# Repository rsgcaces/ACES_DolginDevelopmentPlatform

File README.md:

# RSGC ACES: Dolgin Development Platform (DDP)
 EAGLE and Fusion 360 Design files relating to the RSGC ACES Dolgin Development Platform

## USB to TTL Serial Support
Below is an image of the DDP software serial streaming the 2D readings of the thumb joystick to a Processing sketch that dynamically presents the circular trig functions.   

## Morland Bargraph
The ATtiny84's pins were broken out with specific ACES' devices in mind. The image below shows the Morland Bargraph inserted strategically into the DDP.

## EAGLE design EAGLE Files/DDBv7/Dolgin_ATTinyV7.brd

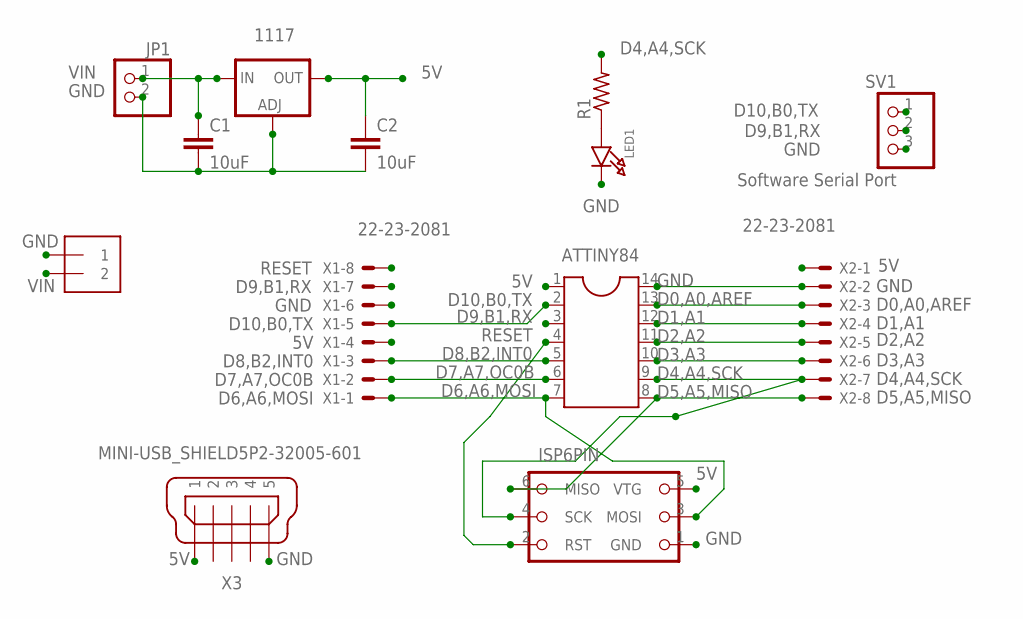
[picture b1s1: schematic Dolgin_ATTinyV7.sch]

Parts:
1117: LM1117SOT223-REFLOW; SOT223-R
ATTINY84: DIL14
C1, C2: 10uF; 1206
H1: ISP_HEADER; ICSP
J1: 1X2-3.5MM
JP1: PINHD-1X2; 1X02
LED1: LED1206; CHIPLED_1206
R1: R-US_R1206; R1206
SV1: Software Serial Port; 1X03/90
X1, X2: 22-23-2081
X3: MINI-USB_SHIELD5P2-32005-601; 32005-601

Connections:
5V: 1117.2 (OUT), ATTINY84.1, C2.1, H1.5 (VTG), X1.4, X2.1, X3.1
D0,A0,AREF: ATTINY84.13, X2.3
D1,A1: ATTINY84.12, X2.4
D2,A2: ATTINY84.11, X2.5
D3,A3: ATTINY84.10, X2.6
D4,A4,SCK: ATTINY84.9, H1.4 (SCK), R1.2, X2.7
D5,A5,MISO: ATTINY84.8, H1.6 (MISO), X2.8
D6,A6,MOSI: ATTINY84.7, H1.3 (MOSI), X1.1
D7,A7,OC0B: ATTINY84.6, X1.2
D8,B2,INT0: ATTINY84.5, X1.3
D9,B1,RX: ATTINY84.3, SV1.2, X1.7
D10,B0,TX: ATTINY84.2, SV1.3, X1.5
GND: 1117.1 (ADJ), ATTINY84.14, C1.2, C2.2, H1.1 (GND), J1.1, JP1.2, LED1.C, SV1.1, X1.6, X2.2, X3.5
unnamed: LED1.A, R1.1
RESET: ATTINY84.4, H1.2 (RST), X1.8
VIN: 1117.3 (IN), C1.1, J1.2, JP1.1

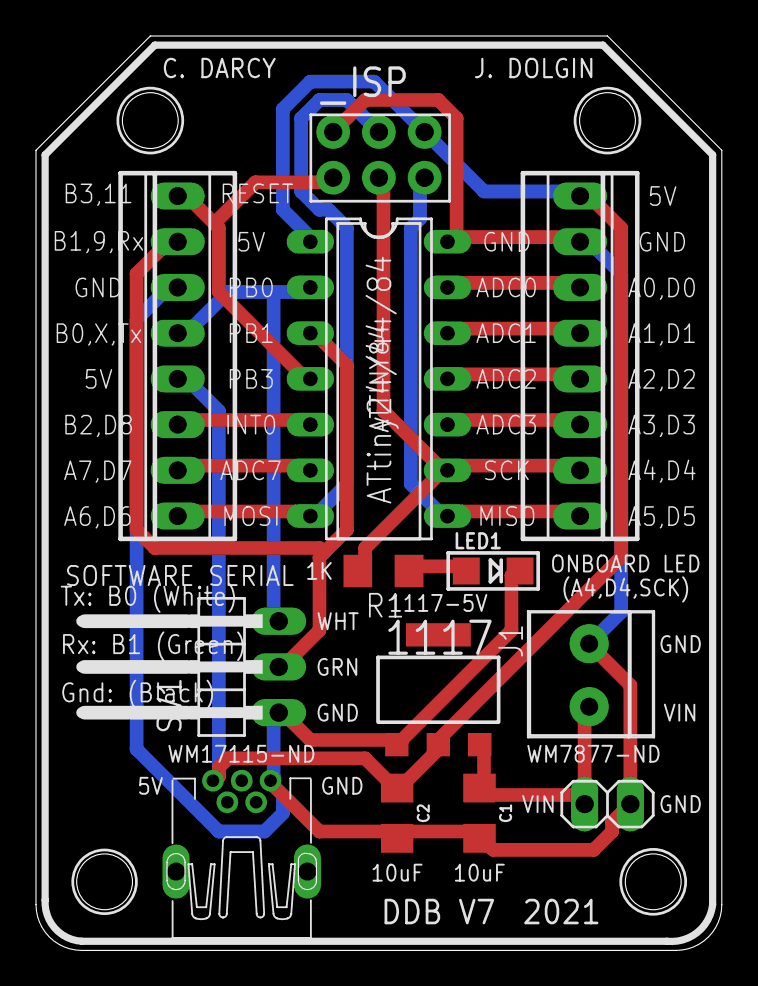
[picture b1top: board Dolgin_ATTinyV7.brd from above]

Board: 2 copper layers, 38.1 x 50.8 mm, 17 parts (1 on the bottom side), 16 nets.

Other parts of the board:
U$1, U$2, U$4: ACES_LOGO_SMALL
U$3: MEDIUM_BSILK_TEXT

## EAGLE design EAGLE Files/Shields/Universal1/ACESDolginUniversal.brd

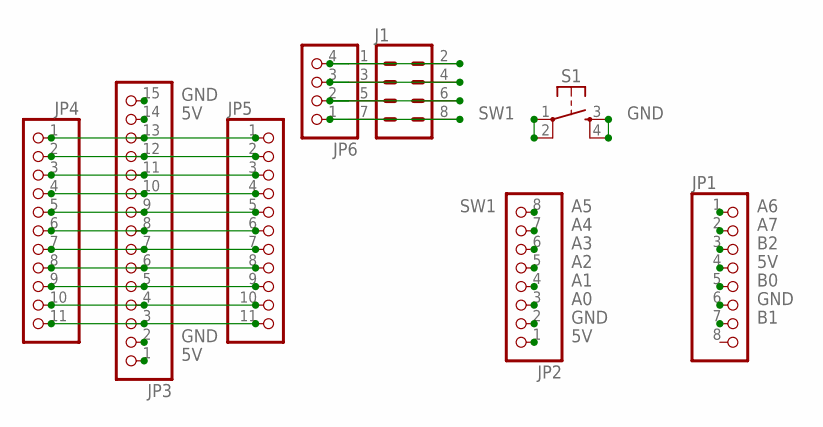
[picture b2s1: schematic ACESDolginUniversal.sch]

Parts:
J1: CONN_04X2; 2X4
JP1, JP2: PINHD-1X8; 1X08
JP3: PINHD-1X15; 1X15
JP4, JP5: PINHD-1X11; 1X11
JP6: PINHD-1X4; 1X04
S1: MOMENTARY_BUTTONS6MMSMALL; TACTILE_SWITCH_PTH_6.0MM

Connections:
5V: JP1.4, JP2.1, JP3.1, JP3.14
A0: JP2.3
A1: JP2.4
A2: JP2.5
A3: JP2.6
A4: JP2.7
A5: JP2.8
A6: JP1.1
A7: JP1.2
B0: JP1.5
B1: JP1.7
B2: JP1.3
GND: JP1.6, JP2.2, JP3.2, JP3.15, S1.3 (S), S1.4 (S1)
unnamed: J1.1, J1.2, JP6.4
unnamed: J1.3, J1.4, JP6.3
unnamed: J1.5, J1.6, JP6.2
unnamed: JP3.13, JP4.1, JP5.1
unnamed: JP3.12, JP4.2, JP5.2
unnamed: JP3.11, JP4.3, JP5.3
unnamed: JP3.10, JP4.4, JP5.4
unnamed: JP3.9, JP4.5, JP5.5
unnamed: JP3.8, JP4.6, JP5.6
unnamed: JP3.7, JP4.7, JP5.7
unnamed: JP3.6, JP4.8, JP5.8
unnamed: JP3.5, JP4.9, JP5.9
unnamed: JP3.4, JP4.10, JP5.10
unnamed: JP3.3, JP4.11, JP5.11
SW1: J1.7, J1.8, JP6.1, S1.1, S1.2 (P1)

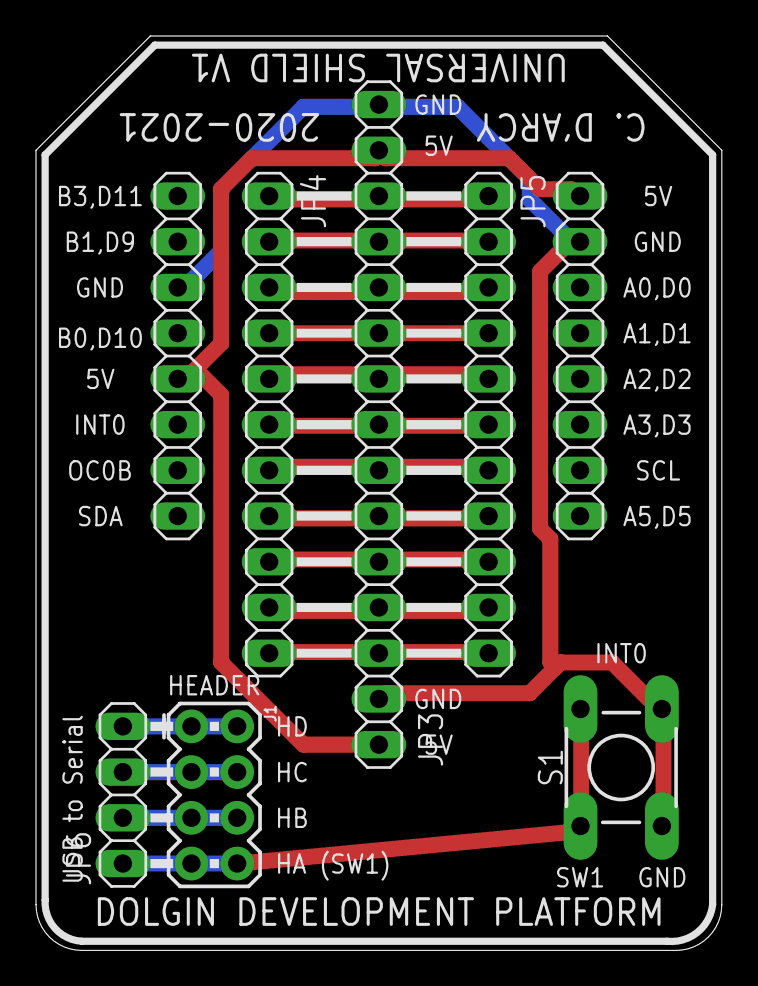
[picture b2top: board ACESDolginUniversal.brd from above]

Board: 2 copper layers, 38.1 x 50.8 mm, 12 parts (0 on the bottom side), 17 nets.

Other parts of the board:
U$1: CAUTION_ELECTRIC
U$2, U$3: SMALL_TSILK_TEXT
U$5: MEDIUM_BSILK_TEXT

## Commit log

2020-01-11 2020 01 11
2020-01-13 Added: 2020 01 13
2020-03-07 Added: 2020 03 07
    Serial support for DDP to the Arduino Serial Monitor and Plotter. Uses the Software Serial library for use with Adafruit's USB-to-Serial Cable (#954).
2020-03-07 Updated: 2020 03 07
2020-03-09 Updated: 2020 03 09
    Example of SoftwareSerial library I/O with the DDP through the use of Adafruit's USB-to-TTL Serial Cable (#954).
2020-05-18 2020 05 18
    Pure assembly version of ADC Shield reading pot or other VD, applying the Double Dabble coversion to BCD and PoVing te result to the displays. Uses Timer 1 OVerflow (1 Hz) as the trigger source
2020-05-18 2020 05 18
    Basic example of Timer 0 Overflow toggles an LED on the DDP at 32 Hz.
2020-05-18 2020 05 18
    Basic example of Timer 1 Overlfow (Normal Mode 0) used to toggle an LED on DDP digital pin 0 at 1Hz.
2020-05-18 Formatted comments
2020-05-18 uploded 2020 05 18
    Use of External Interrupt on the DDP using the PB on the Universal Shield. wired to INT0 (PB2).
2020-05-21 2020 05 22
    AVR Assembly control of a servo's horn position using the ATtiny84's Timer/Counter0 Fast PWM Mode 7. Video support:
    https://www.youtube.com/watch?v=lg2KNSboOUQ&feature=youtu.be
2020-05-21 2020 05 21
2020-12-23 Folder Restructuring
2022-02-24 Update main.asm
    Added: 2022 02 24
2023-03-28 2023 03 29
2023-04-13 Updated for 2023

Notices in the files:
parts and their libraries:
microbuilder: This work is placed in the public domain, and may be freely used for commercial and non-commercial work with the following conditions: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
SparkFun-Capacitors: Licensing: Creative Commons ShareAlike 4.0 International - https://creativecommons.org/licenses/by-sa/4.0
